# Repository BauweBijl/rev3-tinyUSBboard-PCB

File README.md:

# rev3-tinyUSBboard-PCB
TinyUSBboard revision 3 PCB Eagle files (single sided tht bb_1.2_rev3_tinyUSBboard)

This board design is intended to create a tinyUSBboard rev3 as a singlesided PCB with the toner transfer method.
The board allows to use both common available components and the specified (and recommended) components from the tinyUSBboard-rev3 kit.

see also:
http://matrixstorm.com/avr/tinyusbboard/

# Download and Print
Open the tinyusbboard_tht_singlesided.brd in Eagle and select the layers:

1. Bottom
2. Pads
3. Vias
4. Unrouted
5. Dimensions
6. Holes

Hit Ratsnest and print.

# Build
This board design does not come with silkscreen or other information.

To build the board properly it's best to open all layers of tinyusbboard_tht_singlesided.brd in Eagle to view placements, values etc.

Some airwires are created on the toplayer.

# Instructions
Build instructions with images can be found here:
http://wiki.bauwe.nl/TinyUSBboard/Building_TinyUSBboard_rev3_PCB

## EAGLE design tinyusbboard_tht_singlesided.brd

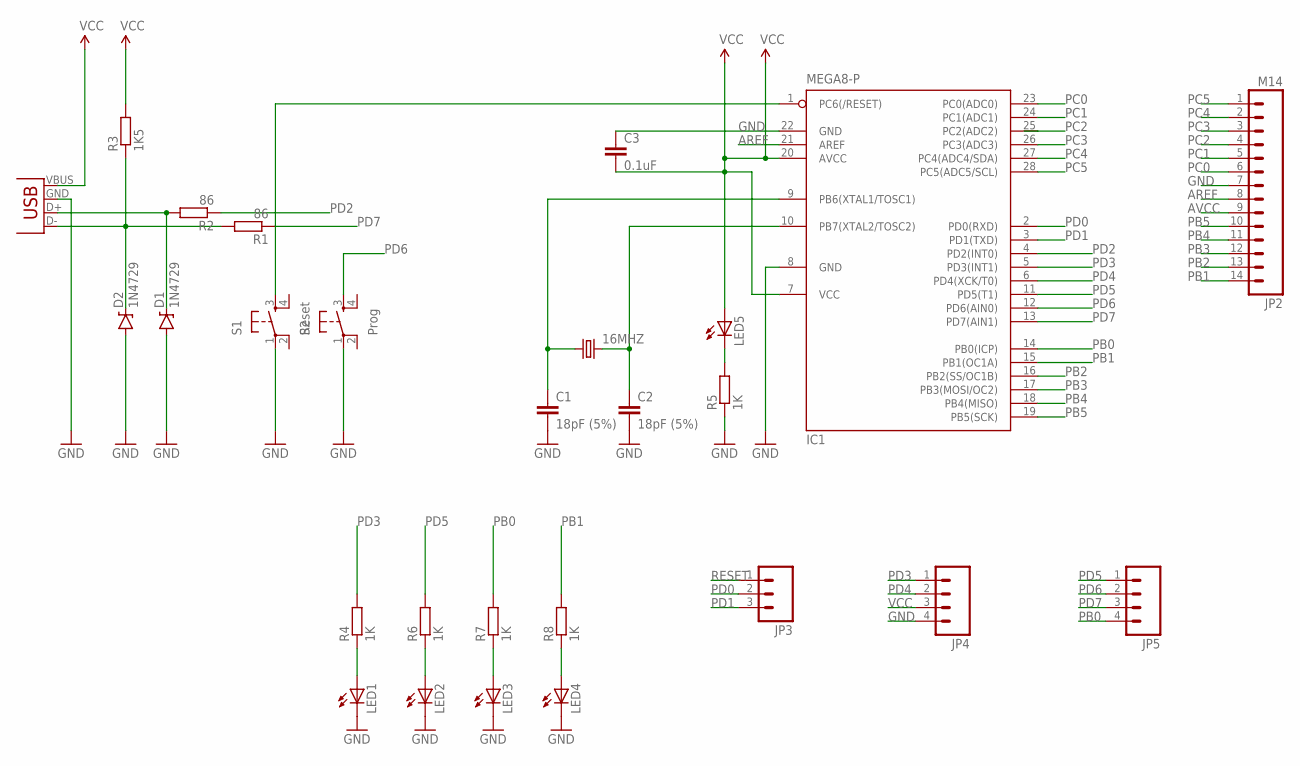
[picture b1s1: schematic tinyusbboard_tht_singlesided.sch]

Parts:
16MHZ: CRYSTALTC26V; TC26V
C1, C2: 18pF (5%); C025-024X044
C3: 0.1uF; C025-024X044
D1, D2: 1N4729; DIODE-ZENER
IC1: MEGA8-P; DIL28-3
JP1: USB-A-H
JP2: M14; 1X14
JP3: M03PTH; 1X03
JP4, JP5: M04PTH; 1X04
LED1, LED2, LED3, LED4, LED5: LED3MM
R1, R2: 86; 0204/7
R3: 1K5; 0204/7
R4, R5, R6, R7, R8: 1K; 0204/7
S1: Reset; TACTILE-PTH
S2: Prog; TACTILE-PTH

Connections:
AREF: IC1.21 (AREF), JP2.8
AVCC: JP2.9
D+: D1.P$1 (C), JP1.D+ (D-), R2.2
D-: D2.P$1 (C), JP1.D- (D+), R1.2, R3.1
GND: C1.2, C2.2, C3.1, D1.P$2 (A), D2.P$2 (A), IC1.8 (GND), IC1.22 (GND), JP1.GND (VBUS), JP2.7, JP4.4, LED1.K (C), LED2.K (C), LED3.K (C), LED4.K (C), R5.1, S1.1, S2.1
unnamed: LED5.K (C), R5.2
unnamed: LED1.A, R4.1
unnamed: LED2.A, R6.1
unnamed: LED3.A, R7.1
unnamed: LED4.A, R8.1
unnamed: 16MHZ.1, C1.1, IC1.9 (PB6(XTAL1/TOSC1))
unnamed: 16MHZ.2, C2.1, IC1.10 (PB7(XTAL2/TOSC2))
PB0: IC1.14 (PB0(ICP)), JP5.4, R7.2
PB1: IC1.15 (PB1(OC1A)), JP2.14, R8.2
PB2: IC1.16 (PB2(SS/OC1B)), JP2.13
PB3: IC1.17 (PB3(MOSI/OC2)), JP2.12
PB4: IC1.18 (PB4(MISO)), JP2.11
PB5: IC1.19 (PB5(SCK)), JP2.10
PC0: IC1.23 (PC0(ADC0)), JP2.6
PC1: IC1.24 (PC1(ADC1)), JP2.5
PC2: IC1.25 (PC2(ADC2)), JP2.4
PC3: IC1.26 (PC3(ADC3)), JP2.3
PC4: IC1.27 (PC4(ADC4/SDA)), JP2.2
PC5: IC1.28 (PC5(ADC5/SCL)), JP2.1
PD0: IC1.2 (PD0(RXD)), JP3.2
PD1: IC1.3 (PD1(TXD)), JP3.3
PD2: IC1.4 (PD2(INT0)), R2.1
PD3: IC1.5 (PD3(INT1)), JP4.1, R4.2
PD4: IC1.6 (PD4(XCK/T0)), JP4.2
PD5: IC1.11 (PD5(T1)), JP5.1, R6.2
PD6: IC1.12 (PD6(AIN0)), JP5.2, S2.3
PD7: IC1.13 (PD7(AIN1)), JP5.3, R1.1
RESET: IC1.1 (PC6(/RESET)), JP3.1, S1.3
VCC: C3.2, IC1.7 (VCC), IC1.20 (AVCC), JP1.VBUS (GND), JP4.3, LED5.A, R3.2

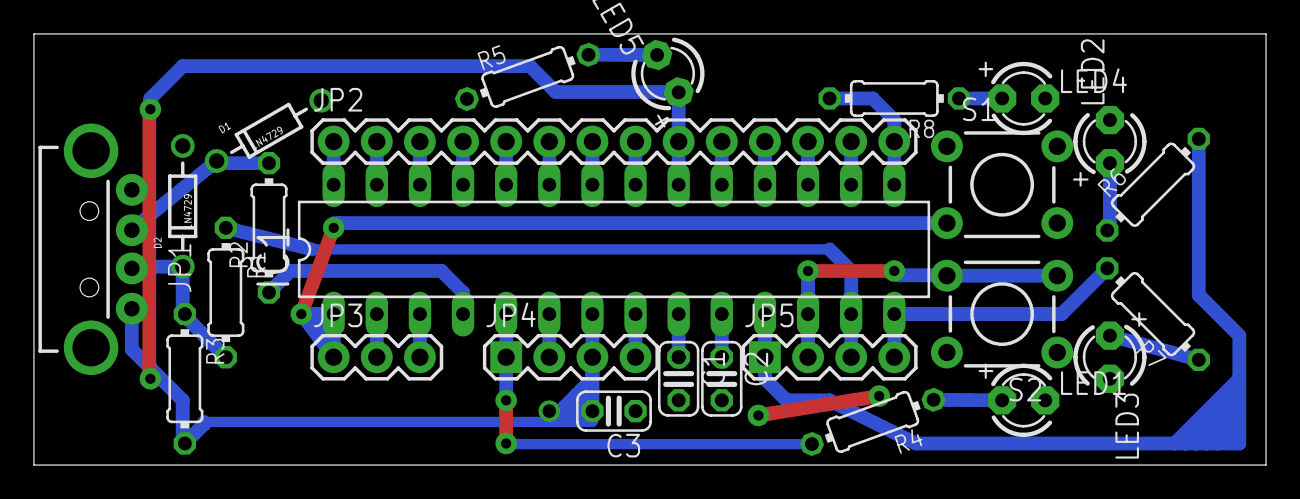
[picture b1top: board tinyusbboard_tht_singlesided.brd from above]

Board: 2 copper layers, 72.6 x 25.4 mm, 27 parts (1 on the bottom side), 33 nets.

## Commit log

2015-02-09 new file: DESCRIPTION new file: tinyusbboard_tht_singlesided.brd new file: tinyusbboard_tht_singlesided.pdf new file: tinyusbboard_tht_singlesided.sch
2015-02-09 modified: README.md
2015-02-10 link to build instructions README.md

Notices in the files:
parts and their libraries:
SparkFun-Retired: Licensing:Creative Commons ShareAlike 4.0 International - https://creativecommons.org/licenses/by-sa/4.0
